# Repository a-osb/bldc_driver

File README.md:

# BLDC Motor Driver
  
This project aims to provide a compact and efficient solution for controlling brushless DC motors in robotics applications. It offers precise feedback and control, making it suitable for tasks that require accurate positioning and smooth motion.

Designed to be compatible with the SimpleFOC project

Based on key components
- DRV8317 integrated mosfet BLDC driver
- STM32G0 Microcontroller
- AS5047D magnetic encoder

Interfaces
- UART
- USB
- CAN

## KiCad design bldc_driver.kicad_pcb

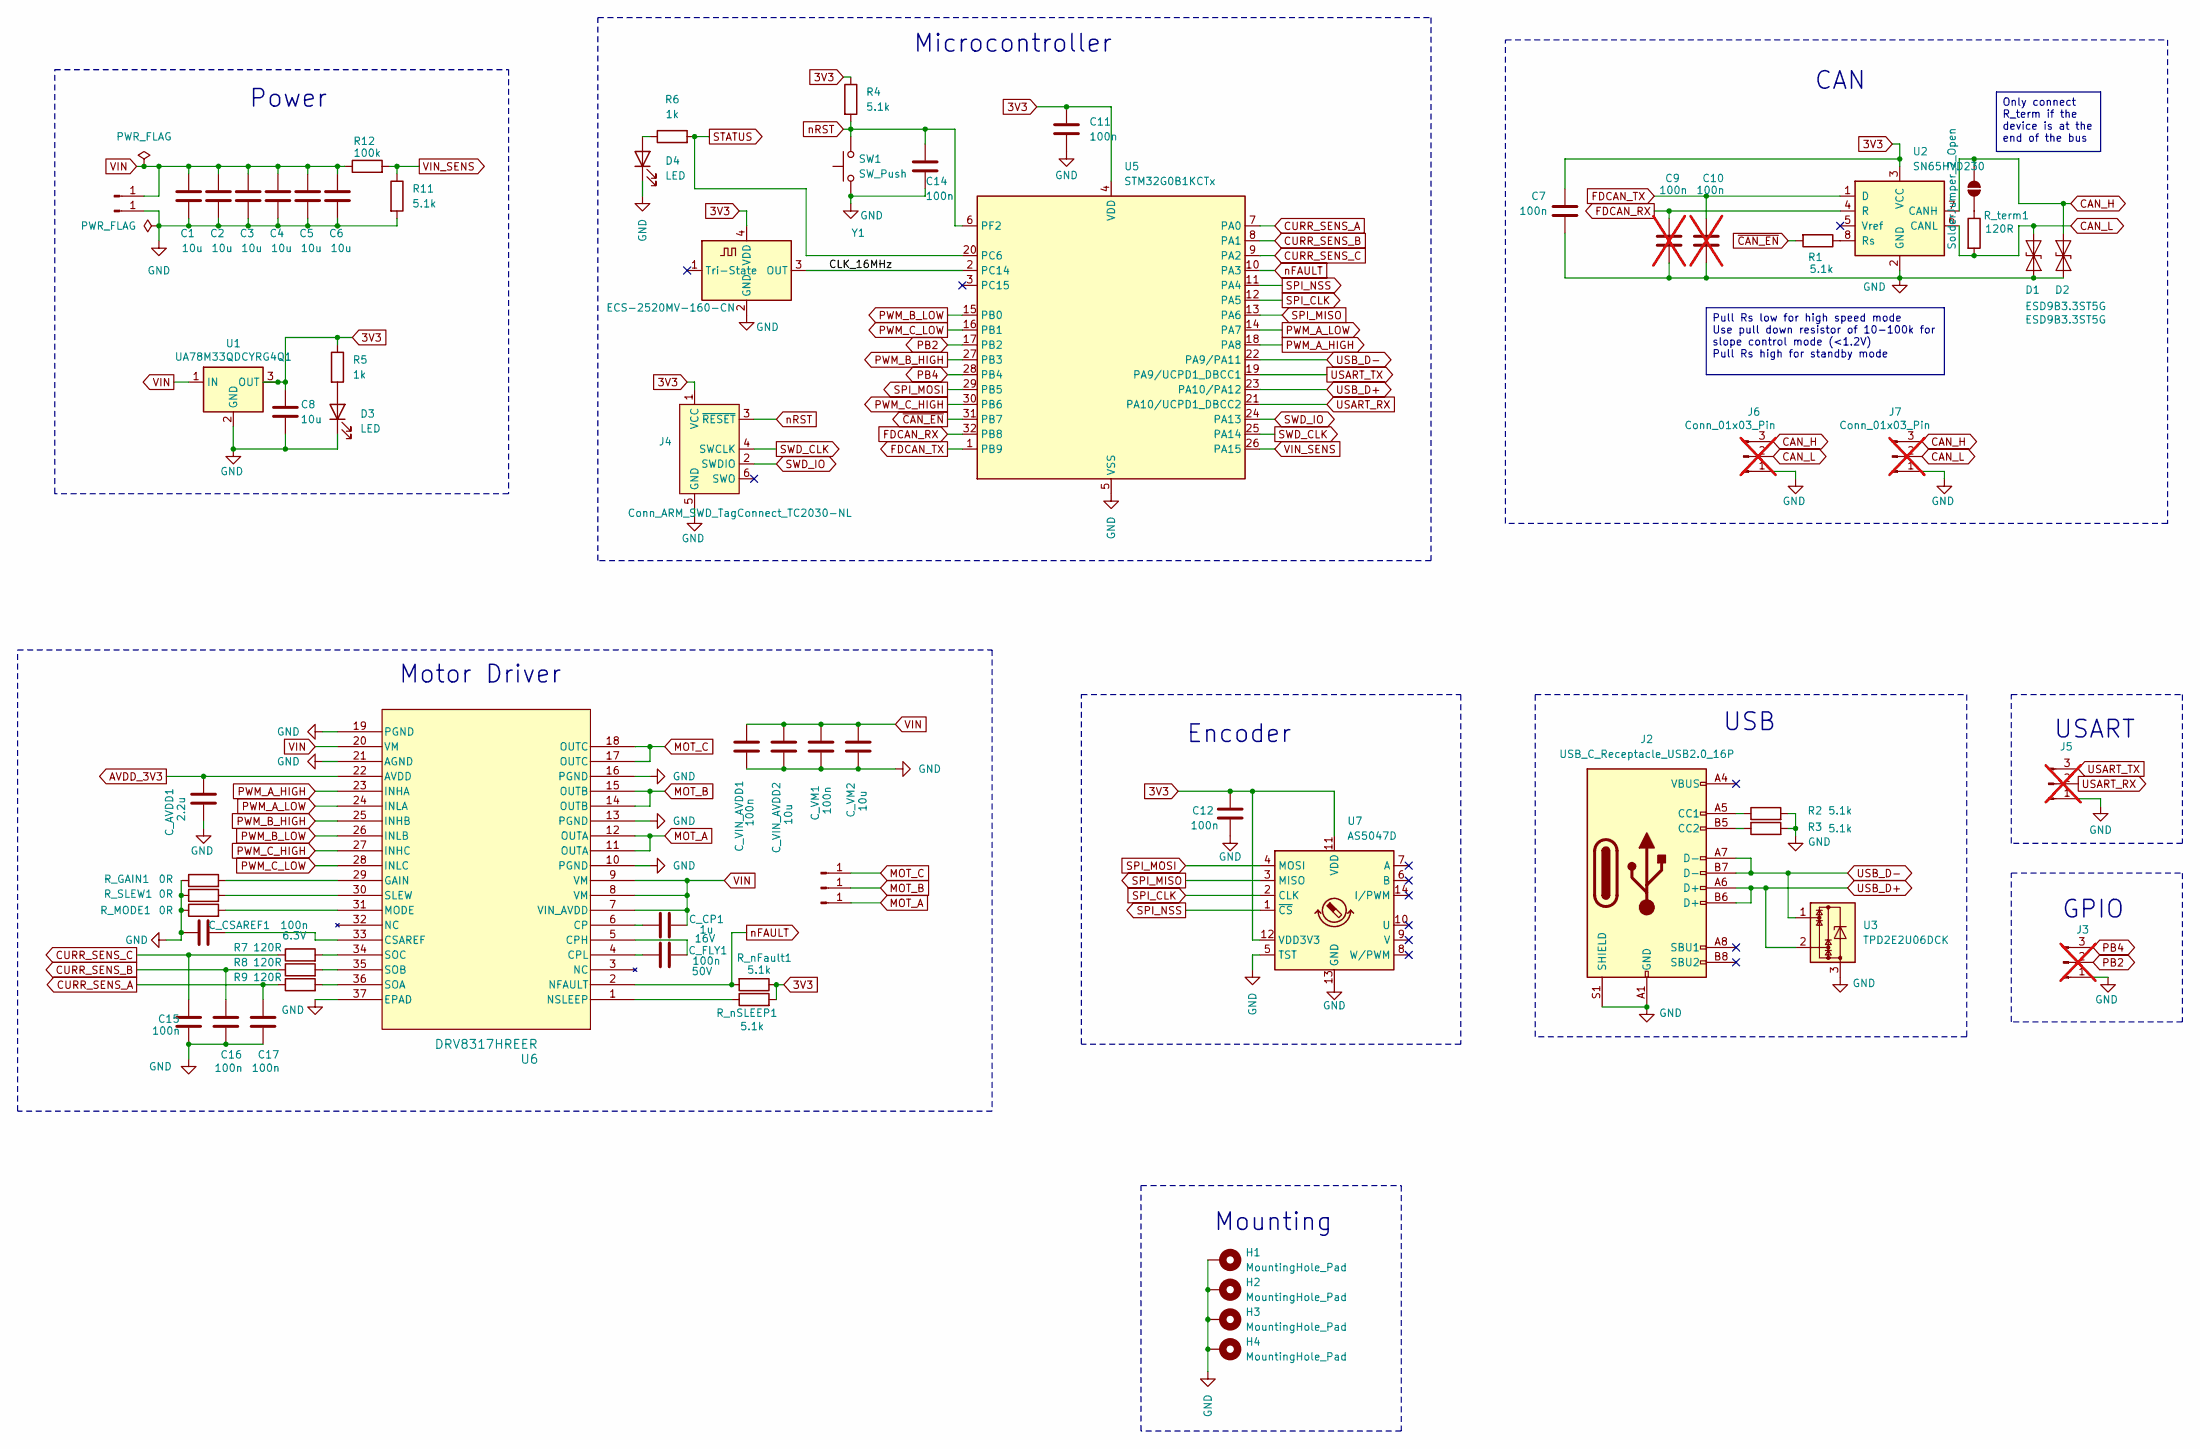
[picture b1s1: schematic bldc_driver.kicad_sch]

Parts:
C1, C2, C3, C4, C5, C6, C8: 10u; C_1210_3225Metric_Pad1.33x2.70mm_HandSolder; Rating 50V
C7, C11, C12, C14, C15, C16, C17: 100n; C_0402_1005Metric_Pad0.74x0.62mm_HandSolder; Rating 6.3V
C9, C10: 100n; C_0402_1005Metric_Pad0.74x0.62mm_HandSolder; not fitted
C_AVDD1: 2.2u; C_0603_1608Metric_Pad1.08x0.95mm_HandSolder; Rating 6.3V
C_CP1: 1u; C_0402_1005Metric_Pad0.74x0.62mm_HandSolder; Rating 16V
C_CSAREF1: 100n; C_0402_1005Metric_Pad0.74x0.62mm_HandSolder; Rating 6.3V
C_FLY1: 100n; C_0402_1005Metric_Pad0.74x0.62mm_HandSolder; Rating 50V
C_VIN_AVDD1: 100n; C_0402_1005Metric_Pad0.74x0.62mm_HandSolder; Rating 50V
C_VIN_AVDD2: 10u; C_0805_2012Metric_Pad1.18x1.45mm_HandSolder; Rating 50V
C_VM1: 100n; C_0402_1005Metric_Pad0.74x0.62mm_HandSolder; Rating 50V
C_VM2: 10u; C_0805_2012Metric_Pad1.18x1.45mm_HandSolder; Rating 50V
D1, D2: ESD9B3.3ST5G; D_SOD-923
D3, D4: LED; LED_0402_1005Metric_Pad0.77x0.64mm_HandSolder
H1, H2, H3, H4: MountingHole_Pad; MountingHole_2.7mm_M2.5_DIN965_Pad_TopBottom
J1, J8, J9, J10, J11: Conn_01x01_Pin; SolderWire-0.75sqmm_1x01_D1.25mm_OD3.5mm
J2: USB_C_Receptacle_USB2.0_16P; USB_C_Receptacle_GCT_USB4110
J3, J5, J6, J7: Conn_01x03_Pin; PinHeader_1x03_P2.54mm_Vertical; not fitted
J4: Conn_ARM_SWD_TagConnect_TC2030-NL; Tag-Connect_TC2030-IDC-NL_2x03_P1.27mm_Vertical
JP1: SolderJumper_2_Open; SolderJumper-2_P1.3mm_Open_TrianglePad1.0x1.5mm
R1, R2, R3, R4, R11: 5.1k; R_0402_1005Metric_Pad0.72x0.64mm_HandSolder
R5, R6: 1k; R_0402_1005Metric_Pad0.72x0.64mm_HandSolder
R7, R8, R9: 120R; R_0402_1005Metric_Pad0.72x0.64mm_HandSolder
R12: 100k; R_0402_1005Metric_Pad0.72x0.64mm_HandSolder
R_GAIN1: 0R; R_0402_1005Metric_Pad0.72x0.64mm_HandSolder
R_MODE1: 0R; R_0402_1005Metric_Pad0.72x0.64mm_HandSolder
R_SLEW1: 0R; R_0402_1005Metric_Pad0.72x0.64mm_HandSolder
R_nFault1: 5.1k; R_0402_1005Metric_Pad0.72x0.64mm_HandSolder
R_nSLEEP1: 5.1k; R_0402_1005Metric_Pad0.72x0.64mm_HandSolder
R_term1: 120R; R_0402_1005Metric_Pad0.72x0.64mm_HandSolder
SW1: SW_Push; SW_Push_1P1T_NO_CK_KMR2
U1: UA78M33QDCYRG4Q1; SOT-223-3_TabPin2
U2: SN65HVD230; SOIC-8_3.9x4.9mm_P1.27mm
U3: TPD2E2U06DCK; SOT-323_SC-70
U5: STM32G0B1KCTx; LQFP-32_7x7mm_P0.8mm
U6: DRV8317HREER; WQFN36_REE_TEX
U7: AS5047D; TSSOP-14_4.4x5mm_P0.65mm
Y1: ECS-2520MV-160-CN; Oscillator_SMD_ECS_2520MV-xxx-xx-4Pin_2.5x2.0mm

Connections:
3V3: C7.1, C8.1, C11.1, C12.1, J4.1 (VCC), R4.1, R5.1, R_nFault1.1, R_nSLEEP1.2, U1.3 (OUT), U2.3 (VCC), U5.4 (VDD), U7.11 (VDD), U7.12 (VDD3V3), Y1.4 (VDD)
/CLK_16MHz: U5.2 (PC14), Y1.3 (OUT)
AVDD_3V3: C_AVDD1.2, U6.22 (AVDD)
CAN_H: D2.2 (A2), J6.3, J7.3, JP1.2 (B), U2.7 (CANH)
CAN_L: D1.2 (A2), J6.2, J7.2, R_term1.2, U2.6 (CANL)
CURR_SENS_A: C17.1, R9.1, U5.7 (PA0)
CURR_SENS_B: C16.1, R8.1, U5.8 (PA1)
CURR_SENS_C: C15.1, R7.1, U5.9 (PA2)
FDCAN_RX: C9.1, U2.4 (R), U5.32 (PB8)
FDCAN_TX: C10.1, U2.1 (D), U5.1 (PB9)
GND: C1.2, C2.2, C3.2, C4.2, C5.2, C6.2, C7.2, C8.2, C9.2, C10.2, C11.2, C12.2, C14.2, C15.2, C16.2, C17.2, C_AVDD1.1, C_CSAREF1.1, C_VIN_AVDD1.2, C_VIN_AVDD2.1, C_VM1.2, C_VM2.2, D1.1 (A1), D2.1 (A1), D3.1 (K), D4.1 (K), H1.1, H2.1, H3.1, H4.1, J1.1, J2.A1 (GND), J2.A12 (GND), J2.B1 (GND), J2.B12 (GND), J2.S1 (SHIELD), J3.1, J4.5 (GND), J5.1, J6.1, J7.1, R2.2, R3.2, R11.2, R_GAIN1.1, R_MODE1.1, R_SLEW1.1, SW1.1, U1.2 (GND), U2.2 (GND), U3.3, U5.5 (VSS), U6.10 (PGND), U6.13 (PGND), U6.16 (PGND), U6.19 (PGND), U6.21 (AGND), U6.37 (EPAD), U7.5 (TST), U7.13 (GND), Y1.2 (GND)
MOT_A: J8.1, U6.11 (OUTA), U6.12 (OUTA)
MOT_B: J9.1, U6.14 (OUTB), U6.15 (OUTB)
MOT_C: J10.1, U6.17 (OUTC), U6.18 (OUTC)
unnamed: D3.2 (A), R5.2
unnamed: D4.2 (A), R6.1
unnamed: J2.A5 (CC1), R2.1
unnamed: J2.B5 (CC2), R3.1
unnamed: JP1.1 (A), R_term1.1
unnamed: R1.1, U2.8 (Rs)
unnamed: C_CP1.1, U6.6 (CP)
unnamed: C_FLY1.2, U6.5 (CPH)
unnamed: C_FLY1.1, U6.4 (CPL)
unnamed: C_CSAREF1.2, U6.33 (CSAREF)
unnamed: R_GAIN1.2, U6.29 (GAIN)
unnamed: R_MODE1.2, U6.31 (MODE)
unnamed: R_nSLEEP1.1, U6.1 (NSLEEP)
unnamed: R_SLEW1.2, U6.30 (SLEW)
unnamed: R9.2, U6.36 (SOA)
unnamed: R8.2, U6.35 (SOB)
unnamed: R7.2, U6.34 (SOC)
PB2: J3.2, U5.17 (PB2)
PB4: J3.3, U5.28 (PB4)
PWM_A_HIGH: U5.18 (PA8), U6.23 (INHA)
PWM_A_LOW: U5.14 (PA7), U6.24 (INLA)
PWM_B_HIGH: U5.27 (PB3), U6.25 (INHB)
PWM_B_LOW: U5.15 (PB0), U6.26 (INLB)
PWM_C_HIGH: U5.30 (PB6), U6.27 (INHC)
PWM_C_LOW: U5.16 (PB1), U6.28 (INLC)
SPI_CLK: U5.12 (PA5), U7.2 (CLK)
SPI_MISO: U5.13 (PA6), U7.3 (MISO)
SPI_MOSI: U5.29 (PB5), U7.4 (MOSI)
SPI_NSS: U5.11 (PA4), U7.1 (~CS)
STATUS: R6.2, U5.20 (PC6)
SWD_CLK: J4.4 (SWCLK), U5.25 (PA14)
SWD_IO: J4.2 (SWDIO), U5.24 (PA13)
USART_RX: J5.2, U5.21 (PA10/UCPD1_DBCC2)
USART_TX: J5.3, U5.19 (PA9/UCPD1_DBCC1)
USB_D+: J2.A6 (D+), J2.B6 (D+), U3.2, U5.23 (PA10/PA12)
USB_D-: J2.A7 (D-), J2.B7 (D-), U3.1, U5.22 (PA9/PA11)
VIN: C1.1, C2.1, C3.1, C4.1, C5.1, C6.1, C_CP1.2, C_VIN_AVDD1.1, C_VIN_AVDD2.2, C_VM1.1, C_VM2.1, J11.1, R12.1, U1.1 (IN), U6.7 (VIN_AVDD), U6.8 (VM), U6.9 (VM), U6.20 (VM)
VIN_SENS: R11.1, R12.2, U5.26 (PA15)
nFAULT: R_nFault1.2, U5.10 (PA3), U6.2 (NFAULT)
nRST: C14.1, J4.3 (~RESET), R4.2, SW1.2, U5.6 (PF2)
~CAN_EN: R1.2, U5.31 (PB7)

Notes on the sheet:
Encoder
USART
USB
CAN
GPIO
Mounting
Motor Driver
Microcontroller
Power
Pull Rs low for high speed mode Use pull down resistor of 10-100k for slope control mode (<1.2V) Pull Rs high for standby mode
Only connect R_term if the device is at the end of the bus

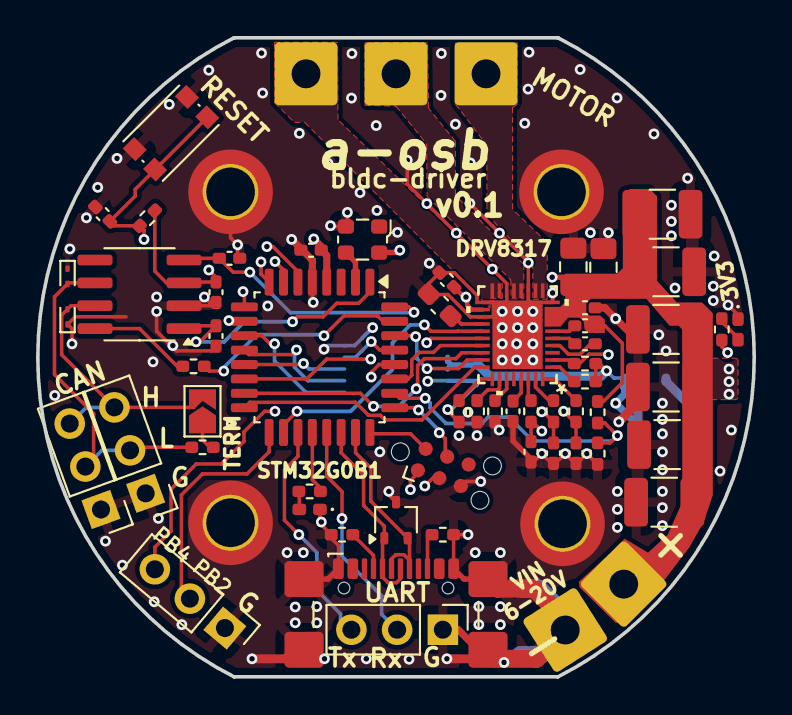
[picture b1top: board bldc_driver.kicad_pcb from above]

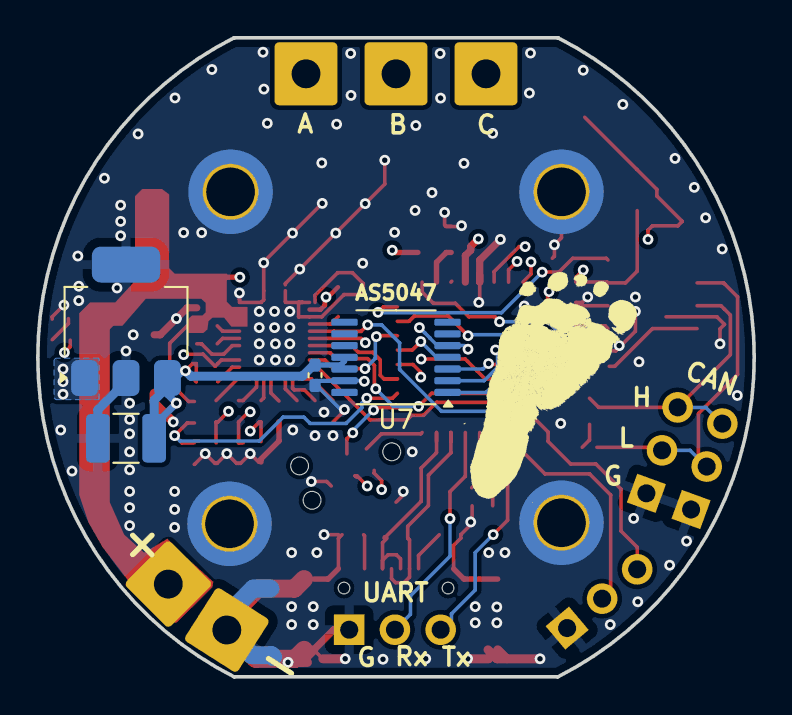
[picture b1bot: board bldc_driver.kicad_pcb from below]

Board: 4 copper layers, 39.8 x 35.5 mm, 69 parts (4 on the bottom side), 55 nets.

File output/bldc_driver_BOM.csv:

"Reference","Qty","Value","Rating","DNP","Exclude from BOM","Exclude from Board","Footprint","Datasheet"
"C1","1","10u","50V","","","","Capacitor_SMD:C_1210_3225Metric_Pad1.33x2.70mm_HandSolder","~"
"C2","1","10u","50V","","","","Capacitor_SMD:C_1210_3225Metric_Pad1.33x2.70mm_HandSolder","~"
"C3","1","10u","50V","","","","Capacitor_SMD:C_1210_3225Metric_Pad1.33x2.70mm_HandSolder","~"
"C4","1","10u","50V","","","","Capacitor_SMD:C_1210_3225Metric_Pad1.33x2.70mm_HandSolder","~"
"C5","1","10u","50V","","","","Capacitor_SMD:C_1210_3225Metric_Pad1.33x2.70mm_HandSolder","~"
"C6","1","10u","50V","","","","Capacitor_SMD:C_1210_3225Metric_Pad1.33x2.70mm_HandSolder","~"
"C7","1","100n","6.3V","","","","Capacitor_SMD:C_0402_1005Metric_Pad0.74x0.62mm_HandSolder","~"
"C8","1","10u","50V","","","","Capacitor_SMD:C_1210_3225Metric_Pad1.33x2.70mm_HandSolder","~"
"C9","1","100n","","DNP","","","Capacitor_SMD:C_0402_1005Metric_Pad0.74x0.62mm_HandSolder","~"
"C10","1","100n","","DNP","","","Capacitor_SMD:C_0402_1005Metric_Pad0.74x0.62mm_HandSolder","~"
"C11","1","100n","6.3V","","","","Capacitor_SMD:C_0402_1005Metric_Pad0.74x0.62mm_HandSolder","~"
"C12","1","100n","6.3V","","","","Capacitor_SMD:C_0402_1005Metric_Pad0.74x0.62mm_HandSolder","~"
"C14","1","100n","6.3V","","","","Capacitor_SMD:C_0402_1005Metric_Pad0.74x0.62mm_HandSolder","~"
"C15","1","100n","6.3V","","","","Capacitor_SMD:C_0402_1005Metric_Pad0.74x0.62mm_HandSolder","~"
"C16","1","100n","6.3V","","","","Capacitor_SMD:C_0402_1005Metric_Pad0.74x0.62mm_HandSolder","~"
"C17","1","100n","6.3V","","","","Capacitor_SMD:C_0402_1005Metric_Pad0.74x0.62mm_HandSolder","~"
"C_AVDD1","1","2.2u","6.3V","","","","Capacitor_SMD:C_0603_1608Metric_Pad1.08x0.95mm_HandSolder","~"
"C_CP1","1","1u","16V","","","","Capacitor_SMD:C_0402_1005Metric_Pad0.74x0.62mm_HandSolder","~"
"C_CSAREF1","1","100n","6.3V","","","","Capacitor_SMD:C_0402_1005Metric_Pad0.74x0.62mm_HandSolder","~"
"C_FLY1","1","100n","50V","","","","Capacitor_SMD:C_0402_1005Metric_Pad0.74x0.62mm_HandSolder","~"
"C_VIN_AVDD1","1","100n","50V","","","","Capacitor_SMD:C_0402_1005Metric_Pad0.74x0.62mm_HandSolder","~"
"C_VIN_AVDD2","1","10u","50V","","","","Capacitor_SMD:C_0805_2012Metric_Pad1.18x1.45mm_HandSolder","~"
"C_VM1","1","100n","50V","","","","Capacitor_SMD:C_0402_1005Metric_Pad0.74x0.62mm_HandSolder","~"
"C_VM2","1","10u","50V","","","","Capacitor_SMD:C_0805_2012Metric_Pad1.18x1.45mm_HandSolder","~"
"D1","1","ESD9B3.3ST5G","","","","","Diode_SMD:D_SOD-923","https://www.onsemi.com/pub/Collateral/ESD9B-D.PDF"
"D2","1","ESD9B3.3ST5G","","","","","Diode_SMD:D_SOD-923","https://www.onsemi.com/pub/Collateral/ESD9B-D.PDF"
"D3","1","LED","","","","","LED_SMD:LED_0402_1005Metric_Pad0.77x0.64mm_HandSolder","~"
"D4","1","LED","","","","","LED_SMD:LED_0402_1005Metric_Pad0.77x0.64mm_HandSolder","~"
"J2","1","USB_C_Receptacle_USB2.0_16P","","","","","bldc_driver:USB_C_Receptacle_GCT_USB4110","https://www.usb.org/sites/default/files/documents/usb_type-c.zip"
"R1","1","5.1k","","","","","Resistor_SMD:R_0402_1005Metric_Pad0.72x0.64mm_HandSolder","~"
"R2","1","5.1k","","","","","Resistor_SMD:R_0402_1005Metric_Pad0.72x0.64mm_HandSolder","~"
"R3","1","5.1k","","","","","Resistor_SMD:R_0402_1005Metric_Pad0.72x0.64mm_HandSolder","~"
"R4","1","5.1k","","","","","Resistor_SMD:R_0402_1005Metric_Pad0.72x0.64mm_HandSolder","~"
"R5","1","1k","","","","","Resistor_SMD:R_0402_1005Metric_Pad0.72x0.64mm_HandSolder","~"
"R6","1","1k","","","","","Resistor_SMD:R_0402_1005Metric_Pad0.72x0.64mm_HandSolder","~"
"R7","1","120R","","","","","Resistor_SMD:R_0402_1005Metric_Pad0.72x0.64mm_HandSolder","~"
"R8","1","120R","","","","","Resistor_SMD:R_0402_1005Metric_Pad0.72x0.64mm_HandSolder","~"
"R9","1","120R","","","","","Resistor_SMD:R_0402_1005Metric_Pad0.72x0.64mm_HandSolder","~"
"R11","1","5.1k","","","","","Resistor_SMD:R_0402_1005Metric_Pad0.72x0.64mm_HandSolder","~"
"R12","1","100k","","","","","Resistor_SMD:R_0402_1005Metric_Pad0.72x0.64mm_HandSolder","~"
"R_GAIN1","1","0R","","","","","Resistor_SMD:R_0402_1005Metric_Pad0.72x0.64mm_HandSolder","~"
"R_MODE1","1","0R","","","","","Resistor_SMD:R_0402_1005Metric_Pad0.72x0.64mm_HandSolder","~"
"R_nFault1","1","5.1k","","","","","Resistor_SMD:R_0402_1005Metric_Pad0.72x0.64mm_HandSolder","~"
"R_nSLEEP1","1","5.1k","","","","","Resistor_SMD:R_0402_1005Metric_Pad0.72x0.64mm_HandSolder","~"
"R_SLEW1","1","0R","","","","","Resistor_SMD:R_0402_1005Metric_Pad0.72x0.64mm_HandSolder","~"
"R_term1","1","120R","","","","","Resistor_SMD:R_0402_1005Metric_Pad0.72x0.64mm_HandSolder","~"
"SW1","1","SW_Push","","","","","Button_Switch_SMD:SW_Push_1P1T_NO_CK_KMR2","~"
"U1","1","UA78M33QDCYRG4Q1","","","","","Package_TO_SOT_SMD:SOT-223-3_TabPin2","https://www.ti.com/lit/gpn/UA78M-Q1"
"U2","1","SN65HVD230","","","","","Package_SO:SOIC-8_3.9x4.9mm_P1.27mm","http://www.ti.com/lit/ds/symlink/sn65hvd230.pdf"
"U3","1","TPD2E2U06DCK","","","","","Package_TO_SOT_SMD:SOT-323_SC-70","http://www.ti.com/lit/ds/symlink/tpd2e2u06.pdf"
"U5","1","STM32G0B1KCTx","","","","","Package_QFP:LQFP-32_7x7mm_P0.8mm","https://www.st.com/resource/en/datasheet/stm32g0b1kc.pdf"
"U6","1","DRV8317HREER","","","","","bldc_driver:WQFN36_REE_TEX","DRV8317HREER"
"U7","1","AS5047D","","","","","Package_SO:TSSOP-14_4.4x5mm_P0.65mm","https://ams.com/documents/20143/36005/AS5047D_DS000394_2-00.pdf"
"Y1","1","ECS-2520MV-160-CN","","","","","bldc_driver:Oscillator_SMD_ECS_2520MV-xxx-xx-4Pin_2.5x2.0mm","https://www.ecsxtal.com/store/pdf/ECS-2520MV.pdf"

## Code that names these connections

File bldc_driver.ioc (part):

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Mcu.Name=STM32G0B1K(B-C-E)Tx
Mcu.Package=LQFP32
Mcu.UserName=STM32G0B1KCTx
PA0.Mode=IN0
PA0.Signal=ADC1_IN0
PA1.Mode=IN1
PA1.Signal=ADC1_IN1
PA10.Mode=Asynchronous
PA10.Signal=USART1_RX
PA11\ [PA9].Mode=Device
PA11\ [PA9].Signal=USB_DM
PA12\ [PA10].Mode=Device
PA12\ [PA10].Signal=USB_DP
PA13.Mode=Serial_Wire
PA13.Signal=SYS_SWDIO
PA14-BOOT0.Mode=Serial_Wire
PA14-BOOT0.Signal=SYS_SWCLK
PA2.Mode=IN2
PA2.Signal=ADC1_IN2
PA4.Mode=NSS_Signal_Hard_Output
PA4.Signal=SPI1_NSS
PA5.Mode=Full_Duplex_Master
PA5.Signal=SPI1_SCK
PA6.Mode=Full_Duplex_Master
PA6.Signal=SPI1_MISO
PA7.Mode=PWM Generation1 CH1 CH1N
PA7.Signal=TIM1_CH1N
PA8.Signal=S_TIM1_CH1
PA9.Mode=Asynchronous
PA9.Signal=USART1_TX
PB0.Mode=PWM Generation2 CH2 CH2N
PB0.Signal=TIM1_CH2N
PB1.Mode=PWM Generation3 CH3 CH3N
PB1.Signal=TIM1_CH3N
PB3.Signal=S_TIM1_CH2
PB5.Mode=Full_Duplex_Master
PB5.Signal=SPI1_MOSI
PB6.Signal=S_TIM1_CH3
PB7.GPIOParameters=GPIO_Label
PB7.GPIO_Label=CAN_EN
PB7.Signal=GPIO_Output
PB8.Mode=FDCAN_Activate
PB8.Signal=FDCAN1_RX
PB9.Mode=FDCAN_Activate
PB9.Signal=FDCAN1_TX
PC14-OSC32_IN\ (PC14).Mode=HSE-External-Clock-Source
PC14-OSC32_IN\ (PC14).Signal=RCC_OSC_IN
PC15-OSC32_OUT\ (PC15).Mode=OSC enable
PC15-OSC32_OUT\ (PC15).Signal=RCC_OSC_EN
PC6.GPIOParameters=GPIO_Label
PC6.GPIO_Label=STATUS
PC6.Signal=GPIO_Output
RCC.HSE_VALUE=16000000
RCC.SYSCLKFreq_VALUE=16000000
board=custom

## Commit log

2025-05-02 Added initial cube mx and kicad proj
2025-05-21 progress on schematic for DRV8317H
2025-05-21 updated ioc
2025-06-03 initial placement of componeents
2025-06-17 schematic and layout mostly done
2025-06-19 for review with outputs
2025-06-23 drc checked
2025-06-23 BOM with ratings
2025-06-23 added pos files
2025-07-02 cut rev 0.1
